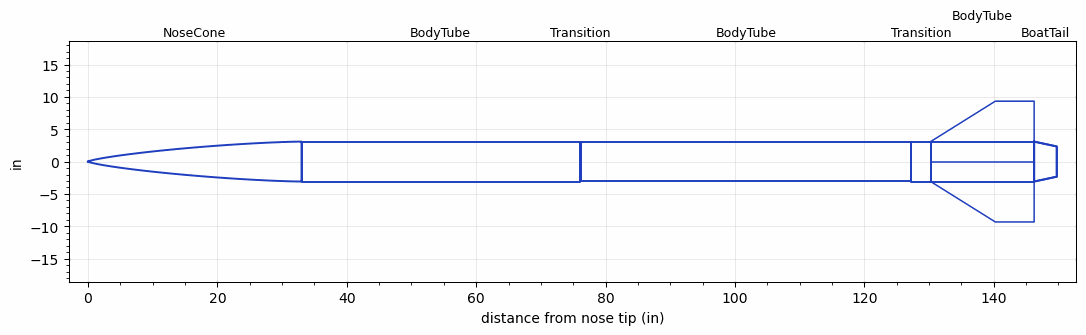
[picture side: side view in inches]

<RASAeroDocument>
 <FileVersion>2</FileVersion>
 <RocketDesign>
  <NoseCone>
   <Length>32.9999</Length>
   <Diameter>6.17</Diameter>
   <Shape>Von Karman Ogive</Shape>
   <Location>0</Location>
  </NoseCone>
  <BodyTube>
   <Length>42.9999</Length>
   <Diameter>6.17</Diameter>
   <Location>32.9999</Location>
  </BodyTube>
  <Transition>
   <Length>0.25</Length>
   <Diameter>6</Diameter>
   <Location>75.9998</Location>
   <RearDiameter>6</RearDiameter>
  </Transition>
  <BodyTube>
   <Length>50.9999</Length>
   <Diameter>6</Diameter>
   <Location>76.2498</Location>
  </BodyTube>
  <Transition>
   <Length>3</Length>
   <Diameter>6.17</Diameter>
   <Location>127.2497</Location>
   <RearDiameter>6.17</RearDiameter>
  </Transition>
  <BodyTube>
   <Length>16</Length>
   <Diameter>6.17</Diameter>
   <Location>130.2497</Location>
   <BoattailLength>3.5</BoattailLength>
   <BoattailRearDiameter>4.67</BoattailRearDiameter>
   <Fin>
    <Count>4</Count>
    <Chord>16</Chord>
    <Span>6.25</Span>
    <SweepDistance>10</SweepDistance>
    <TipChord>6</TipChord>
    <Thickness>0.5</Thickness>
    <LERadius>0.05</LERadius>
    <Location>16</Location>
    <AirfoilSection>Hexagonal</AirfoilSection>
    <FX1>1.5</FX1>
    <FX3>1.5</FX3>
   </Fin>
  </BodyTube>
  <BoatTail>
   <Length>3.5</Length>
   <Diameter>6.17</Diameter>
   <RearDiameter>4.67</RearDiameter>
   <Location>146.2497</Location>
  </BoatTail>
  <Surface>Rough Camouflage Paint</Surface>
  <ModifiedBarrowman>False</ModifiedBarrowman>
  <Turbulence>False</Turbulence>
  <UseBooster1>False</UseBooster1>
  <UseBooster2>False</UseBooster2>
 </RocketDesign>
 <LaunchSite>
  <Altitude>0</Altitude>
  <Pressure>29.9214</Pressure>
  <RodAngle>0</RodAngle>
  <RodLength>20</RodLength>
  <Temperature>59</Temperature>
  <WindSpeed>5</WindSpeed>
 </LaunchSite>
 <Recovery>
  <Altitude1>0</Altitude1>
  <Altitude2>0</Altitude2>
  <DeviceType1>None</DeviceType1>
  <DeviceType2>None</DeviceType2>
  <Event1>False</Event1>
  <Event2>False</Event2>
  <Size1>0</Size1>
  <Size2>0</Size2>
  <EventType1>None</EventType1>
  <EventType2>None</EventType2>
  <CD1>0</CD1>
  <CD2>0</CD2>
 </Recovery>
 <SimulationList>
  <Simulation>
   <SustainerEngine>P7204  (MIT)</SustainerEngine>
   <SustainerLaunchWt>232.17</SustainerLaunchWt>
   <SustainerCG>105.82</SustainerCG>
   <SustainerIgnitionDelay>0</SustainerIgnitionDelay>
   <Booster1SeparationDelay>0</Booster1SeparationDelay>
   <Booster1IgnitionDelay>0</Booster1IgnitionDelay>
   <IncludeBooster1>False</IncludeBooster1>
   <Booster2Delay>0</Booster2Delay>
   <IncludeBooster2>False</IncludeBooster2>
   <TimetoApogee>44.35856</TimetoApogee>
   <MaxAltitude>33290.71</MaxAltitude>
   <MaxVelocity>1825.766</MaxVelocity>
  </Simulation>
 </SimulationList>
</RASAeroDocument>
